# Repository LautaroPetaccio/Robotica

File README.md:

# Robótica en la escuela - Robot simulator

The *Robot simulator* is a tool for teaching programing basics by letting the user play and explore with the blocks it provides for the robot's movement and sensor's control.

The code from the simulator can be exported to Arduino code to program the project's robot.

The simulator uses MelonJS as the gaming library for the robot, Blocky ([Ardublockly](http://ardublockly.embeddedlog.com)) for the blocky styled language, Bootstrap and others.

Blocky, introduces an easier way to give the robot instructions, eliminating the need to write, that could be hard to some people that haven't had experience with computers before, making the focus in the logics of programming itself.

## Setup

1. Install nodejs.

  The robot simulator was developed and tested with the nodejs version 7.10.0. It should work with older versions aswell.

  To install the required version, we recommend using a package manager. The instructions to do so are provided in the node website https://nodejs.org/en/download/package-manager/ .

2. Check npm installation (installed automatically with nodejs):

  ```
  $ npm -v
  4.2.0
  ```

3. Install bower and check installation.

  ```
  $ sudo npm install -g bower
  $ bower -v
  1.8.0
  ```

4. Install gulp and check installation.

  ```
  $ sudo npm install -g gulp
  $ gulp -v
  [...] CLI version 3.9.1
  ```

5. Install dev local dependencies (run from the project's root directory).

  ```
  $ npm install
  [...]
  ```

6. Install front-end dependencies (run from the project's root directory).

  ```
  $ bower install
  [...]
  ```

## Running

* Build distributable version.

  ```
  $ gulp build
  $ ls dist/
  ```

* Run app locally for development. There's no need to run `gulp build` first.

  ```
  $ gulp serve
  ```
   A new window or tab will open in the default browser, showing a running version of the app. Any changes on html files, scripts, or styles in the src folder will update automatically the running app without needing a manual page refresh.

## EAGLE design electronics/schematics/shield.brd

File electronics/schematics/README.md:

# Robotica en la Escuela - Arduino Shield
The electronic part of the proyect consists of an Arduino Shield created using the Eagle CAD software.
The shield has:
- Headers for the three sonar HC-SR04 sensors.
- A L293D H-Bridge for controlling the motors.
- Screw sockets for the battery holder.

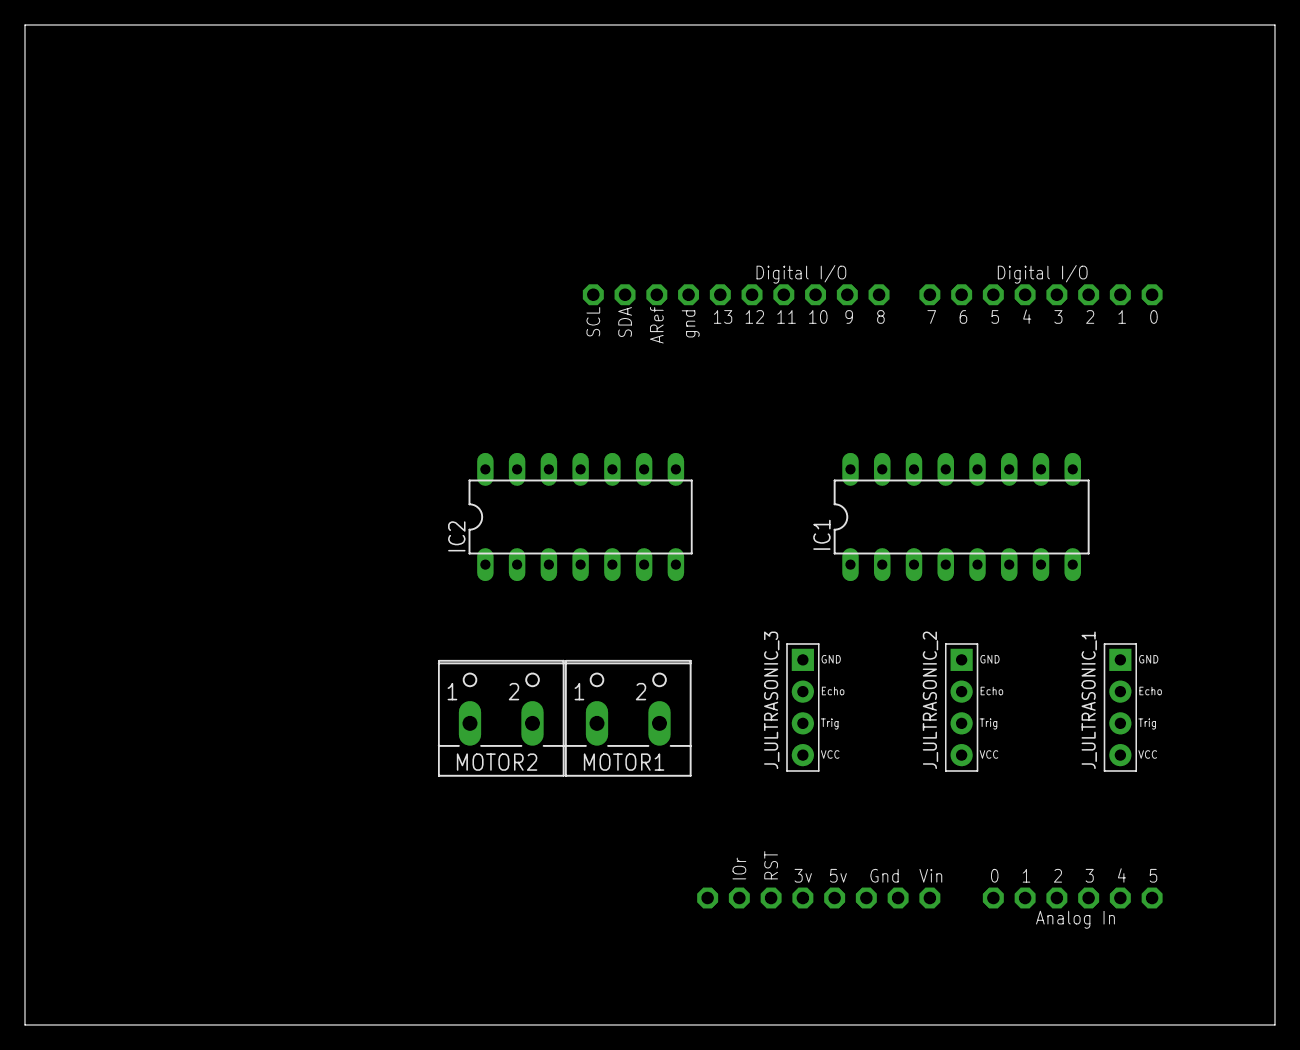
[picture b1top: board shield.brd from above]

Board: 2 copper layers, 100.0 x 80.0 mm, 8 parts (0 on the bottom side), 19 nets, no tracks yet.

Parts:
IC1: L293D; DIL16
IC2: 74HC00N; DIL14
J_ULTRASONIC_1, J_ULTRASONIC_2, J_ULTRASONIC_3: HC-SR04; HC-SR04_FOOTPRINT
MOTOR1, MOTOR2: W237-102
U1: ARDUINOR3-BPLACE

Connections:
1-2EN: IC1.1, U1.D11
1A: IC1.2, U1.D13
2A: IC1.7, U1.D12
3-4EN: IC1.9, U1.D10
3A: IC1.10, U1.D9
4A: IC1.15, U1.D8
9VCC: IC1.8, U1.VIN
GND: IC1.4, IC1.5, IC1.12, IC1.13, IC2.7, J_ULTRASONIC_1.GND, J_ULTRASONIC_2.GND, J_ULTRASONIC_3.GND, U1.GND, U1.GND1, U1.GND2
unnamed: J_ULTRASONIC_1.TRIG, U1.A0
unnamed: J_ULTRASONIC_1.ECHO, U1.A1
unnamed: J_ULTRASONIC_2.TRIG, U1.A2
unnamed: J_ULTRASONIC_2.ECHO, U1.A3
unnamed: J_ULTRASONIC_3.TRIG, U1.A4
unnamed: J_ULTRASONIC_3.ECHO, U1.A5
unnamed: IC1.3, MOTOR1.1
unnamed: IC1.6, MOTOR1.2
unnamed: IC1.14, MOTOR2.1
unnamed: IC1.11, MOTOR2.2
VCC: IC1.16, IC2.14, J_ULTRASONIC_1.VCC, J_ULTRASONIC_2.VCC, J_ULTRASONIC_3.VCC, U1.5V

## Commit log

2015-10-11 Fixed if
2015-10-11 Refactoring
2015-10-19 Added readme
2016-03-17 Changed interface, added load code and save code
2016-03-17 Added blocky to the interface
2016-03-18 Added blockly to libraries
2016-03-18 Changed sensor block to dropdown
2016-03-18 Changed order in robotica_motor
2016-03-18 Changed robotica block colors
2016-03-19 Adapted the game entities to the new interpreter
2016-03-19 Added the code execution state to the gmae
2016-03-19 Adapted the play/pause/stop buttons
2016-03-19 Added the javascript interpreted using in the simulator
2016-03-19 Fixed value inputs for the robotica blocks
2016-03-19 Fixed returning order incorrectly
2016-03-19 Removed the old parser and AST walker
2016-03-19 Corrected typo
2016-03-19 Added color to Robotica in the toolbox
2016-03-19 Deleted unnecessary javascript code
2016-03-19 New readme
2016-03-19 Added new objective
2016-04-10 Deleted tasks
2016-04-14 Updated melonJS to 3.01
2016-04-15 Game cleanup and first box added to the map to test collisions
2016-04-25 MelonJS file
2016-04-26 arregle las colisiones y cambie el sensor para que diga adelante y atras en vez de arriba y abajo
2016-04-27 Agregado plugin de debugging - resolves #19
2016-04-27 Cambiada indentacion a 2 espacios
2016-04-27 Revert "arregle las colisiones y cambie el sensor para que diga adelante y atras en vez de arriba y abajo"
2016-04-27 Traducciones y tildes - resolves #3
2016-04-27 colisiones - resolves #2
2016-04-27 renombres a los sensores arriba y abajo - resolves #21
2016-04-27 Ruedas invertidas- resolves #16
2016-05-05 Selección y traducción de bloques - resolves #13
2016-05-05 Correcciones basicas de estilo
2016-05-05 Arregla posicionamiento vertical del simulador
2016-05-06 Introduce modo para pantalla chica
2016-05-06 Agrega modificaciones a navbar y detalles
2016-05-06 Agrega cambios pisados y fix de boton
2016-05-06 Evita que se cierre la ventana con los controles
2016-05-07 Removidos logs antiguos
2016-05-07 El boton ejecutar solo funciona cuando hay codigo - resolves #31
2016-05-07 Agrega redondeo
2016-05-10 Agregado build system - gulpjs. Issue #9.
    Mergeado con master; hay que mergear las funcionalidades implementadas en los otros branches cuando esten listas.
2016-05-10 Fix. Lenguaje Blockly a español.
2016-05-11 Mergeando con master.
2016-05-14 Agrega mas tiempo para evitar descolocar item
2016-05-16 Rename.
2016-05-16 Quito padding de home panels.
2016-05-17 Cambio automatico de layout on resize.
2016-05-17 Cambio layout default para tamanos pantalla md.
2016-05-21 Creadas draw y el canvas, necesarios para el tracer - resolves #15
2016-05-21 Bloques para el tracer
2016-05-21 Agregada logica para el interpretador del tracer y bloques fisicos
2016-05-22 Actualizo el readme.
2016-05-22 Cambio en la shape del robot - resolves #27
2016-05-22 Agregadas nuevas shapes para la representacion de los sensores
2016-05-22 Nuevo checkeo de limites basado en el mapa
2016-05-22 Fix en la traduccion del bloque sensor
2016-05-22 Movimiento de las shapes del robot en base al movimiento de las ruedas
2016-05-22 Muevo la carpeta de plugins a src/.
2016-05-22 Modificado sistema de colisiones para actuar como sensores
2016-05-22 Panel de debug actualizado con parametros del robot
2016-05-22 Plugin de lineas
2016-05-22 Agregados vector y line al pool
2016-05-22 Plugin de lineas y sensado de limites de mapa
2016-05-23 Cargar acorn.js y interpreter.js alternativos para obtener la funcion asincronica
2016-05-23 Fix en el bloque sensor y bloques de debugging
2016-05-23 Logica asincronica para utilizar el bloque sensor en tiempo y forma - resolves #14
2016-05-23 Loading screen
2016-05-24 Fix de inversion de potencia en ruedas
2016-05-24 Fix al race condition entre ejecucion de instrucciones y resetteo de nivel
2016-05-24 El bloque traza habilitada ahora tiene un bloque enganchado por default
2016-05-24 Limpieza de codigo
2016-05-24 Agrego funcionalidad de guardar / cargar codigo y un programa como ejemplo.
2016-05-24 Agrego modal para elegir nombre de archivo.
2016-05-25 El bloque motor ahora tiene valores por defecto - resolves #44
2016-05-25 Presionar ENTER en el campo de texto del modal lleva a guardar el codigo
2016-05-25 Arregla tildes
2016-05-25 Descripción de bloques de robótica
2016-05-25 Fuerzo que los plugins se carguen antes que game.js.
2016-05-27 limite de velocidad en 100
2016-05-27 Fix cambio de layout al clickear el simulador.
2016-05-28 Muevo la lógica de overflow a runtime. Agrego notificaciones con toasters.
2016-05-29 Nuevas dependencias
2016-05-29 Nueva organizacion de mapas
2016-05-29 Nueva task de gulp para generar el modal con los mapas
2016-05-29 Template para el modal
2016-05-29 Implementacion del modal en la interfaz
2016-05-31 Fix en el tamanio del area de colision
2016-05-31 Nuevo mapa con obstaculos en el circuito
2016-05-31 Cambio de niveles
2016-05-31 El resize del mapa ahora se realiza con doble click
2016-05-31 agrego un mapa con forma de laberinto
2016-06-01 Cambio overflow a saturación (y la notificacion).
2016-06-01 Fix el problema de que no se veía el modal en mobile.
2016-06-01 Mejoro el manejo de promises en los metodos render de los modulos. Issue #54.
2016-06-08 Fix para los sensores no funcionando en la pared izqueirda - resolves #59
2016-06-08 Fix en los limites de movimiento del robot, el sensado ahora da 0 al chocar un borde
2016-06-08 Mostrar la posicion del robot redondeada
2016-06-08 Arreglo el bug del issue 58. Fix #58.
2016-06-09 Shortcuts - resolves #62
2016-06-09 Modulo de ayuda y modal para FAQ
2016-06-11 mapa para practicar ciclos en la sdc
2016-06-12 Agrego programita para resolver el mapa zig zag.
2016-06-12 Ordeno por estado: 0, 1, 2.
2016-06-12 Agrego libreria para manejar los shortcuts.
2016-06-12 Refactor navbar.js. Agrego shortcut para cambio de mapa.
2016-06-12 Refactor shortcut bindings a navbar.js
2016-06-12 Cambiados shortcuts de ingles a espaniol
2016-06-14 Introduce interfaz integrada con material design
2016-06-14 Introduce ajustes y animaciones a botones de control
2016-06-15 Modifica el expanded view de mapa para pantallas chicas
2016-06-18 Mejora colores de blockly y navbar
2016-06-18 Evita la seleccion de texto en los botones
2016-06-19 Cambiado color de los bloques de matematicas y actualizados los bloques y generadores
2016-06-19 Ignorar closure library
2016-06-19 Color de las barras de desplazamiento
2016-06-20 Cambio de colores de bloques matematicos al inicializar Blockly
2016-06-20 Cambios en tipografia de navbar
2016-06-20 Cambia el tamaño de la fuente de botones
2016-06-21 Cambia favicon por uno con transparencia
2016-06-21 Deja el titulo mas corto
2016-06-21 Agregada task de assets para navbar
2016-06-21 Introduce logo nuevo
2016-06-21 Saco los botones de Ayuda y exportar.
2016-06-21 Fix: enable/disable boton stop.
2016-06-21 Agrego programita solucion para el laberinto.
2016-06-23 Refactorizacion de codigo - desacoplamiento de navbar y simulator
2016-06-23 Refactoring de la inicializacion del interprete JS
2016-06-25 Implementacion del HUD que muestra los datos del robot y sus sensores
2016-06-25 agrego un mapa
2016-06-27 Modal de configuraciones
2016-06-27 Removido archivo de backup
2016-07-01 Si se cambia el codigo al pausar, se reinicia la ejecucion
2016-07-01 Implementacion del modo de visualizacion de sensores en melonjs
2016-07-06 Limpiar el workspace de Blockly al cambiar de mapa
2016-07-19 Revert al último commit pre-SdC. Los nuevos commits estan en branch dev.
2016-07-20 Separo estilos del simulador y blockly en funcion del tamaño de pantalla.
2016-07-20 Fix animaciones.
2016-07-20 Fix bordes blancos aleatorios alrededor de blockly y simu.
2016-07-20 Cambio de mapa: Agrego dialog para pedir confirmacion antes de borrar el codigo.
2016-07-20 Fix: navbar no se podia clickear en mobile. Esconder modal al accionar el checkbox.
2016-07-23 Removidos logs
2016-07-23 Elimino bordes.
2016-08-05 Gulp ahora utiliza newer para procesar archivos. Resolves #78
2016-08-05 Saco el efecto shake. Arreglo botones redondos.
2016-08-05 Agrego mdi sin que rompa el build.
2016-08-05 Fix el path de los fonts de mdi en fonts.js
2016-08-05 Redo un par de cosas que se borraron sin querer.
2016-08-06 Agregado directorio de css para mdi
2016-08-06 Cambiados iconos de botones en el navbar.
2016-08-06 Arreglado el alineamiento vertical de los botones de play.
2016-08-07 Filtrando mdi/css/* en la task general de styles. Seguia pasando el crash en el build.
2016-08-07 Deduplico los botones de play-pause-stop en navbar.
2016-08-07 Navbar: botones derechos aparecen en la misma linea en modo colapsado.
2016-08-08 Commit inicial de la parte electronica del proyecto.
2016-08-29 Resolves #82
2016-09-08 FileSave ahora contiene el formateo de nombres de archivos
2016-09-08 Modulo para el modal de descargas. Implementadas descargas XML y Arduino
2016-09-08 Agregado comportamiento del boton exportar al navbar
2016-09-09 Cambiado Blockly de Google por Blockly de Ardublocky
2016-09-09 Adaptacion de los bloques custom al Blockly Ardublockly
2016-09-09 Agregada la funcionalidad de exportar codigo al modal
2016-09-10 Agregado loop al codigo Arduino al ser exportado para corresponder con el simulador
2016-09-23 Nuevo mapa para estacionar
2016-10-07 Checkeo de colisiones en el primer update. Resolves #86
2017-05-07 Fix a las notificaciones no apareciendo cuando se excede la velocidad
2017-05-26 Se aplica uglify primero a cada archivo para debugguear mejor
2017-05-27 Cargar los assets de blockly desde ardublockly
2017-05-27 Agregadas dependencias de backbone y handlebars
2017-05-27 Generacion de HTML por medio de templates con handlebars
2017-05-27 Templates para la generacion de HTML
2017-05-27 Uso parcial de templates con modulos originales
2017-05-29 Cambios en templates
2017-05-29 Modelos de backbone
2017-05-29 Vistas de Backbone
2017-05-29 Cambios en el orden de generacion del archivos JS de la app
2017-05-29 Inicializacion de la aplicacion mediante las estructuras de backbone
2017-05-29 Eliminadas comillas en los nombres de las propiedades del objeto
2017-05-29 Limpieza de archivos y directorios
2017-05-29 Re-estructuracion de estilos e imagenes
2017-05-30 Codigo base + generacion de codigo mejorada
2017-05-30 Fix para el orden de ejecucion de los scripts
2017-05-30 Borrados logs
2017-05-30 Fixes para la expansion y arrastre del simulador
2017-06-03 Removida compile-handlebars, agregado gulp-hb y handlebars layouts
2017-06-03 Modularizado el template del modal
2017-06-03 Se tienen en cuentas los templates a la hora de utilizar gulp serve. Se compila el html solo si se realizo un cambio
2017-06-03 Removido log innecesario
2017-06-04 El robot ahora se mueve como el simulador
2017-06-04 El movimiento del robot se realiza utilizando la velocidad angular maxima del robot fisico
2017-06-05 Emprolijando la generacion de codigo
2017-06-05 Arreglado bug donde se agregaban listeners al workspace pero no se removian
2017-06-05 Fixes para guardar y cargar codigo
2017-06-07 Fix para generacion de codigo erronea
2017-06-07 Borrados logs en la exportacion de codigo
2017-06-24 Actualizadas dependencias de npm
2017-06-25 Actualizadas las dependencias no conlfictivas - Resolves #93
2017-06-25 Cambios en el readme
2017-06-25 Arreglada expresion regular para extraer codigo arduino de la funcion setup
2017-06-25 Removido log
2017-07-13 Cambiado sensor por sense. Resolves #97
